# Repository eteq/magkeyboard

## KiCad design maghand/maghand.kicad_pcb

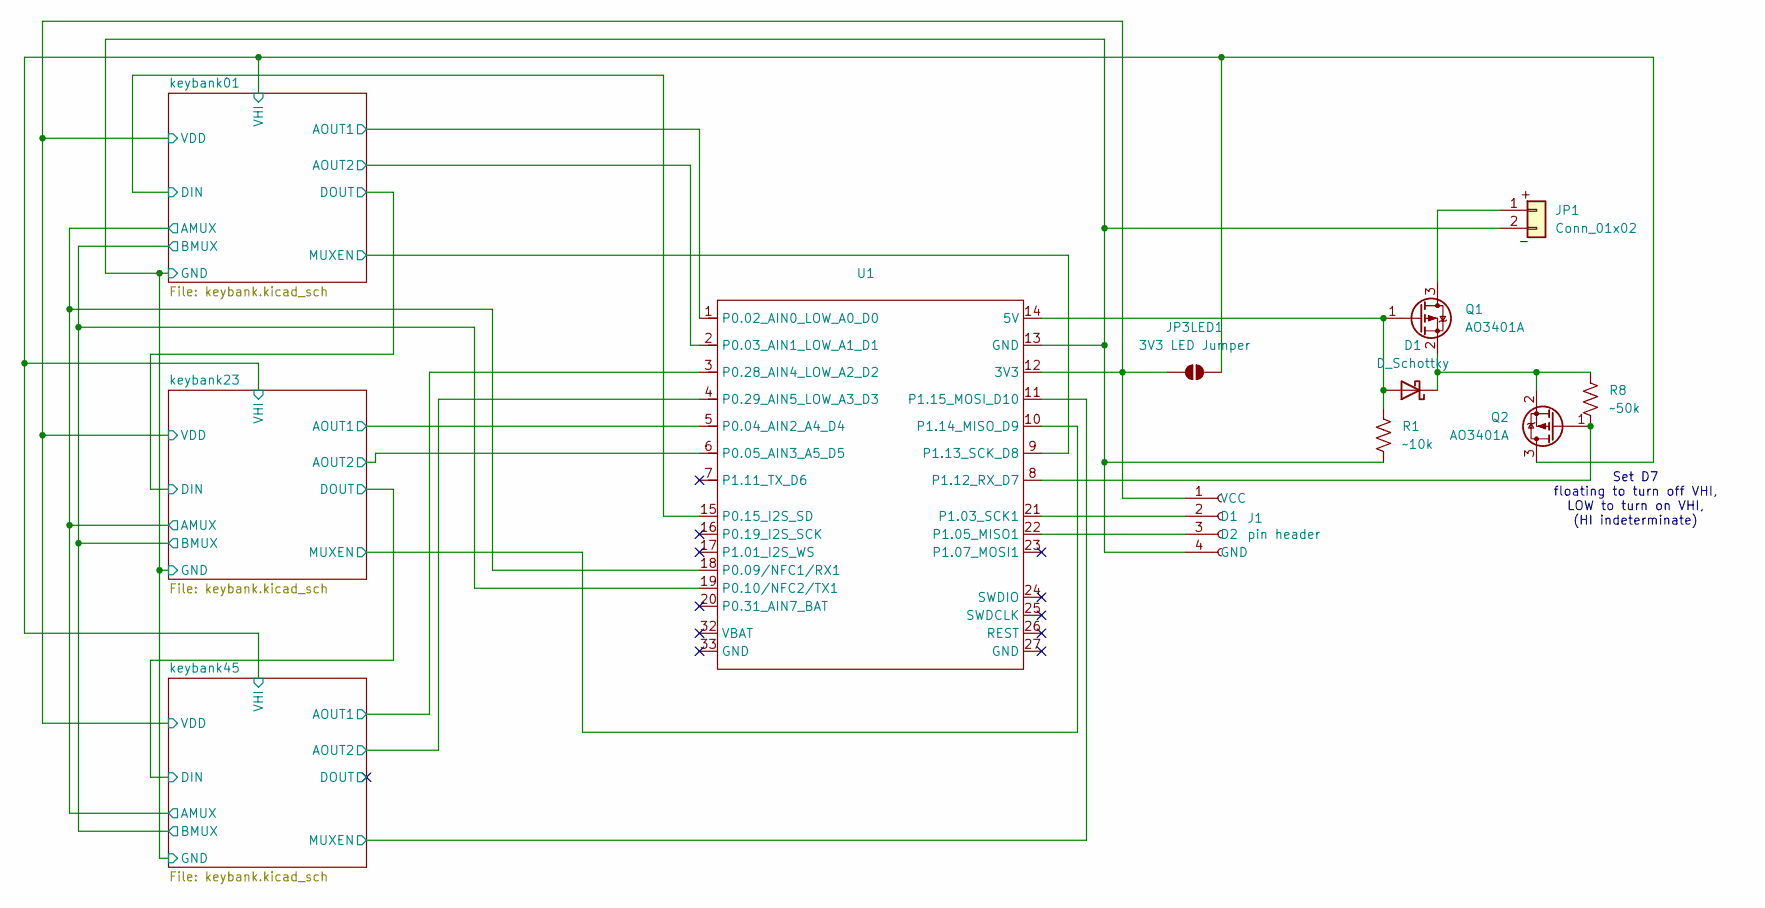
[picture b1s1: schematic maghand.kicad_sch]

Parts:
D1: D_Schottky; D_Powermite_AK
J1: pin header; PinSocket_1x04_P2.54mm_Vertical
JP1: Conn_01x02; JST_PH_S2B-PH-SM4-TB_1x02-1MP_P2.00mm_Horizontal
JP3LED1: 3V3 LED Jumper; SolderJumper-2_P1.3mm_Open_TrianglePad1.0x1.5mm
Q1, Q2: AO3401A; SOT-23
R1: ~10k; R_0805_2012Metric_Pad1.20x1.40mm_HandSolder
R8: ~50k; R_0805_2012Metric_Pad1.20x1.40mm_HandSolder
U1: XIAO-nRF52840-Plus-SMD_bathole

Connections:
/keybank01/AMUX: U1.18 (P0.09/NFC1/RX1); also elsewhere on the board
/keybank01/AOUT1: U1.1 (P0.02_AIN0_LOW_A0_D0); also elsewhere on the board
/keybank01/AOUT2: U1.2 (P0.03_AIN1_LOW_A1_D1); also elsewhere on the board
/keybank01/BMUX: U1.19 (P0.10/NFC2/TX1); also elsewhere on the board
/keybank01/DIN: U1.15 (P0.15_I2S_SD); also elsewhere on the board
/keybank01/GND: J1.4 (GND), JP1.2 (BAT-), R1.2, U1.13 (GND); also elsewhere on the board
/keybank01/MUXEN: U1.9 (P1.13_SCK_D8); also elsewhere on the board
/keybank01/VDD: J1.1 (VCC), JP3LED1.2 (B), U1.12 (3V3); also elsewhere on the board
/keybank01/VHI: JP3LED1.1 (A), Q2.3 (D); also elsewhere on the board
/keybank23/AOUT1: U1.5 (P0.04_AIN2_A4_D4); also elsewhere on the board
/keybank23/AOUT2: U1.6 (P0.05_AIN3_A5_D5); also elsewhere on the board
/keybank23/MUXEN: U1.10 (P1.14_MISO_D9); also elsewhere on the board
/keybank45/AOUT1: U1.3 (P0.28_AIN4_LOW_A2_D2); also elsewhere on the board
/keybank45/AOUT2: U1.4 (P0.29_AIN5_LOW_A3_D3); also elsewhere on the board
/keybank45/MUXEN: U1.11 (P1.15_MOSI_D10); also elsewhere on the board
unnamed: D1.2 (A), Q1.1 (G), R1.1, U1.14 (5V)
unnamed: D1.1 (K), Q1.2 (S), Q2.2 (S), R8.1
unnamed: J1.2 (D1), U1.21 (P1.03_SCK1)
unnamed: J1.3 (D2), U1.22 (P1.05_MISO1)
unnamed: JP1.1 (BAT+), Q1.3 (D)
unnamed: Q2.1 (G), R8.2, U1.8 (P1.12_RX_D7)

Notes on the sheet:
Set D7 floating to turn off VHI, LOW to turn on VHI, (HI indeterminate)

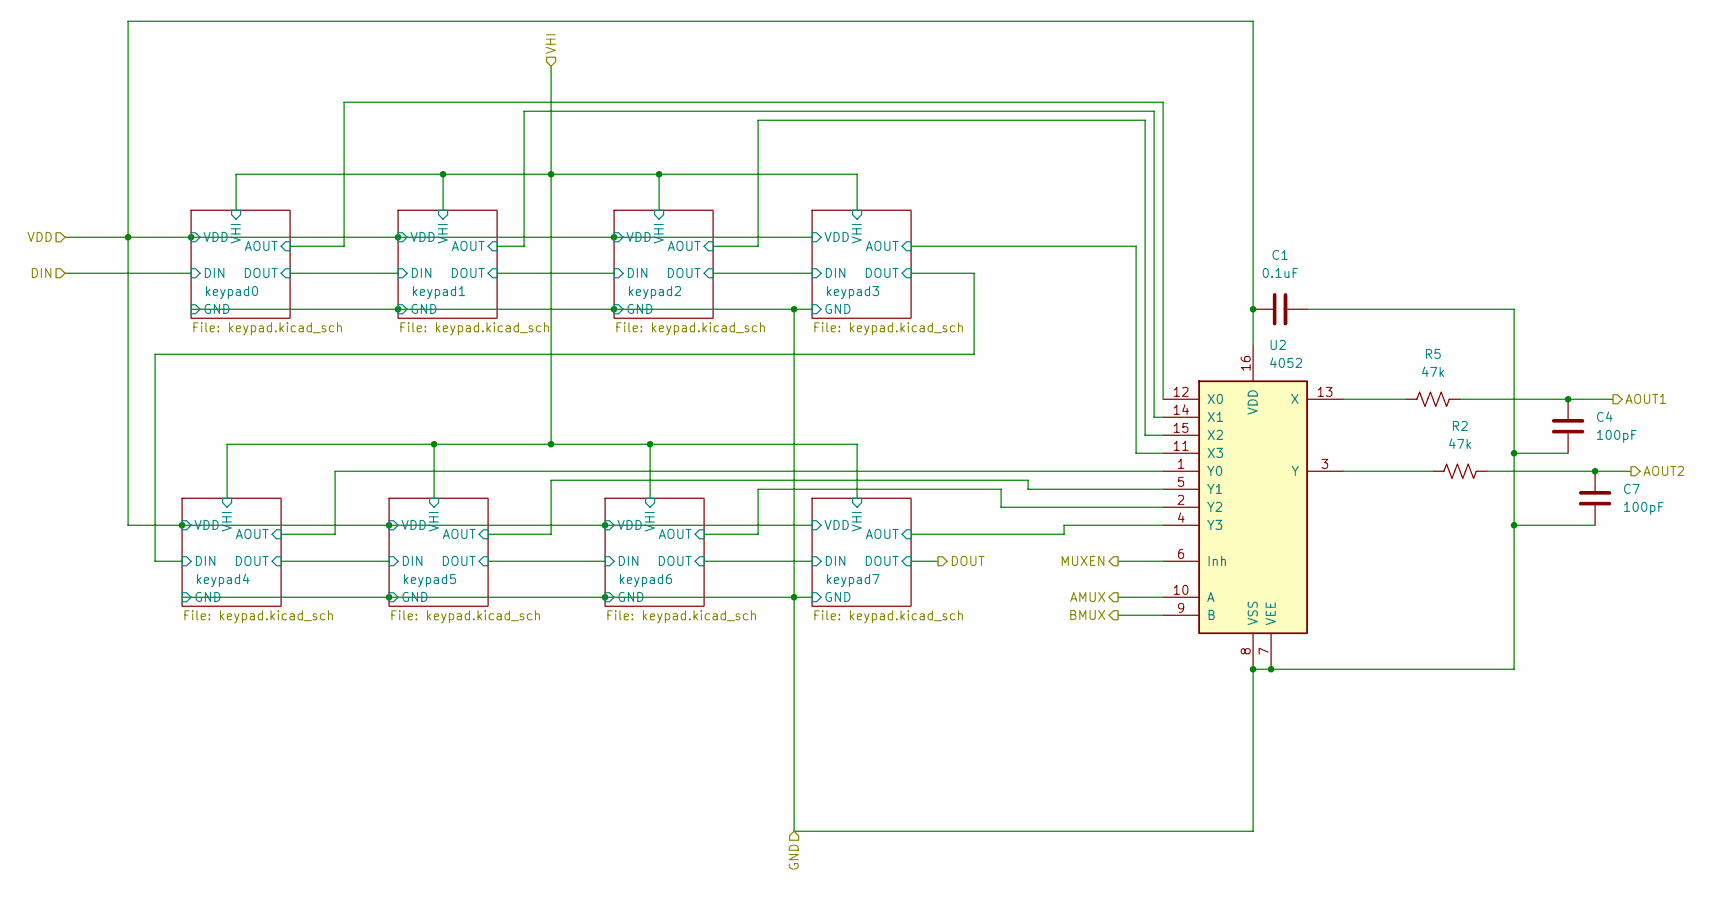
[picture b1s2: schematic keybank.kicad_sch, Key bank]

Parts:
C1: 0.1uF; C_0805_2012Metric_Pad1.18x1.45mm_HandSolder
C4, C7: 100pF; C_0805_2012Metric_Pad1.18x1.45mm_HandSolder
R2, R5: 47k; R_0805_2012Metric_Pad1.20x1.40mm_HandSolder
U2: 4052; SOIC-16_3.9x9.9mm_P1.27mm

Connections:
/keybank01/AMUX: U2.10 (A); also elsewhere on the board
/keybank01/AOUT1: C4.1, R5.2; also elsewhere on the board
/keybank01/AOUT2: C7.1, R2.2; also elsewhere on the board
/keybank01/BMUX: U2.9 (B); also elsewhere on the board
/keybank01/GND: C1.1, C4.2, C7.2, U2.7 (VEE), U2.8 (VSS); also elsewhere on the board
/keybank01/MUXEN: U2.6 (Inh); also elsewhere on the board
/keybank01/VDD: C1.2, U2.16 (VDD); also elsewhere on the board
/keybank01/keypad0/AOUT: U2.12 (X0); also elsewhere on the board
/keybank01/keypad1/AOUT: U2.14 (X1); also elsewhere on the board
/keybank01/keypad2/AOUT: U2.15 (X2); also elsewhere on the board
/keybank01/keypad3/AOUT: U2.11 (X3); also elsewhere on the board
/keybank01/keypad4/AOUT: U2.1 (Y0); also elsewhere on the board
/keybank01/keypad5/AOUT: U2.5 (Y1); also elsewhere on the board
/keybank01/keypad6/AOUT: U2.2 (Y2); also elsewhere on the board
/keybank01/keypad7/AOUT: U2.4 (Y3); also elsewhere on the board
unnamed: R5.1, U2.13 (X)
unnamed: R2.1, U2.3 (Y)

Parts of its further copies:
C2, C3: 0.1uF; C_0805_2012Metric_Pad1.18x1.45mm_HandSolder
C5, C6, C8, C9: 100pF; C_0805_2012Metric_Pad1.18x1.45mm_HandSolder
R3, R4, R6, R7: 47k; R_0805_2012Metric_Pad1.20x1.40mm_HandSolder
U3, U4: 4052; SOIC-16_3.9x9.9mm_P1.27mm

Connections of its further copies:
/keybank01/AMUX: U3.10 (A), U4.10 (A); also elsewhere on the board
/keybank01/BMUX: U3.9 (B), U4.9 (B); also elsewhere on the board
/keybank01/GND: C2.1, C3.1, C5.2, C6.2, C8.2, C9.2, U3.7 (VEE), U3.8 (VSS), U4.7 (VEE), U4.8 (VSS); also elsewhere on the board
/keybank01/VDD: C2.2, C3.2, U3.16 (VDD), U4.16 (VDD); also elsewhere on the board
/keybank23/AOUT1: C5.1, R6.2; also elsewhere on the board
/keybank23/AOUT2: C8.1, R3.2; also elsewhere on the board
/keybank23/MUXEN: U3.6 (Inh); also elsewhere on the board
/keybank23/keypad0/AOUT: U3.12 (X0); also elsewhere on the board
/keybank23/keypad1/AOUT: U3.14 (X1); also elsewhere on the board
/keybank23/keypad2/AOUT: U3.15 (X2); also elsewhere on the board
/keybank23/keypad3/AOUT: U3.11 (X3); also elsewhere on the board
/keybank23/keypad4/AOUT: U3.1 (Y0); also elsewhere on the board
/keybank23/keypad5/AOUT: U3.5 (Y1); also elsewhere on the board
/keybank23/keypad6/AOUT: U3.2 (Y2); also elsewhere on the board
/keybank23/keypad7/AOUT: U3.4 (Y3); also elsewhere on the board
/keybank45/AOUT1: C6.1, R7.2; also elsewhere on the board
/keybank45/AOUT2: C9.1, R4.2; also elsewhere on the board
/keybank45/MUXEN: U4.6 (Inh); also elsewhere on the board
/keybank45/keypad0/AOUT: U4.12 (X0); also elsewhere on the board
/keybank45/keypad1/AOUT: U4.14 (X1); also elsewhere on the board
/keybank45/keypad2/AOUT: U4.15 (X2); also elsewhere on the board
/keybank45/keypad3/AOUT: U4.11 (X3); also elsewhere on the board
/keybank45/keypad4/AOUT: U4.1 (Y0); also elsewhere on the board
/keybank45/keypad5/AOUT: U4.5 (Y1); also elsewhere on the board
/keybank45/keypad6/AOUT: U4.2 (Y2); also elsewhere on the board
/keybank45/keypad7/AOUT: U4.4 (Y3)
unnamed: R6.1, U3.13 (X)
unnamed: R3.1, U3.3 (Y)
unnamed: R7.1, U4.13 (X)
unnamed: R4.1, U4.3 (Y)

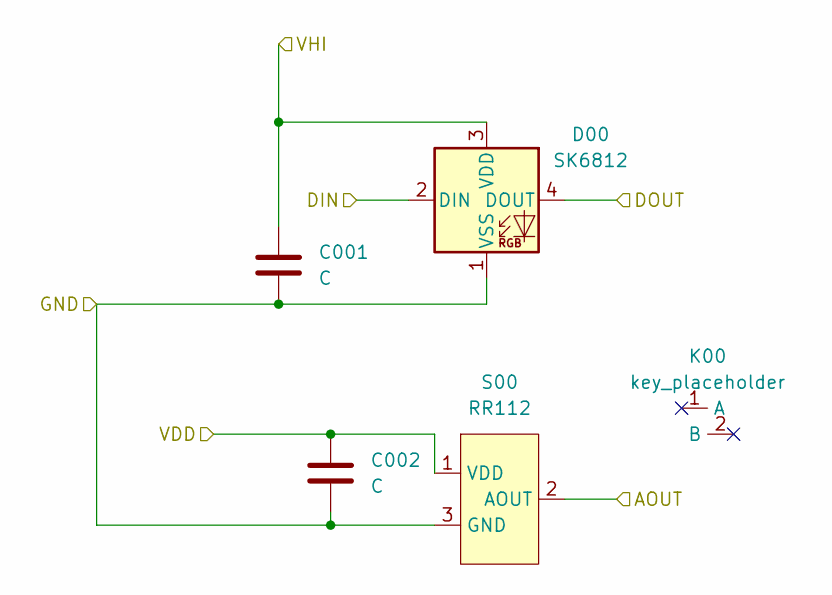
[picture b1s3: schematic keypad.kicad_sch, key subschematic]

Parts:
C001, C002: C; C_0805_2012Metric_Pad1.18x1.45mm_HandSolder
D00: SK6812; LED_SK6812_PLCC4_5.0x5.0mm_P3.2mm
K00: key_placeholder; Key Holder
S00: RR112; SOT-23_Handsoldering

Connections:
/keybank01/DIN: D00.2 (DIN); also elsewhere on the board
/keybank01/GND: C001.2, C002.2, D00.1 (VSS), S00.3 (GND); also elsewhere on the board
/keybank01/VDD: C002.1, S00.1 (VDD); also elsewhere on the board
/keybank01/VHI: C001.1, D00.3 (VDD); also elsewhere on the board
/keybank01/keypad0/AOUT: S00.2 (AOUT); also elsewhere on the board
/keybank01/keypad0/DOUT: D00.4 (DOUT); also elsewhere on the board

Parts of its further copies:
C011, C012, C021, C022, C031, C032, C101, C102, C111, C112, C121, C122, C131, C132, C201, C202, C211, C212, C221, C222, C231, C232, C301, C302, C311, C312, C321, C322, C331, C332, C401, C402, C411, C412, C421, C422, C431, C432, C501, C502, C511, C512, C521, C522: C; C_0805_2012Metric_Pad1.18x1.45mm_HandSolder
D01, D02, D03, D10, D11, D12, D13, D20, D21, D22, D23, D30, D31, D32, D33, D40, D41, D42, D43, D50, D51, D52: SK6812; LED_SK6812_PLCC4_5.0x5.0mm_P3.2mm
K01, K02, K03, K10, K11, K12, K13, K20, K21, K22, K23, K30, K31, K32, K33, K40, K41, K42, K43, K50, K51, K52: key_placeholder; Key Holder
S01, S02, S03, S10, S11, S12, S13, S20, S21, S22, S23, S30, S31, S32, S33, S40, S41, S42, S43, S50, S51, S52: RR112; SOT-23_Handsoldering

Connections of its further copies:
/keybank01/DOUT: D13.4 (DOUT), D20.2 (DIN)
/keybank01/GND: C011.2, C012.2, C021.2, C022.2, C031.2, C032.2, C101.2, C102.2, C111.2, C112.2, C121.2, C122.2, C131.2, C132.2, C201.2, C202.2, C211.2, C212.2, C221.2, C222.2, C231.2, C232.2, C301.2, C302.2, C311.2, C312.2, C321.2, C322.2, C331.2, C332.2, C401.2, C402.2, C411.2, C412.2, C421.2, C422.2, C431.2, C432.2, C501.2, C502.2, C511.2, C512.2, C521.2, C522.2, D01.1 (VSS), D02.1 (VSS), D03.1 (VSS), D10.1 (VSS), D11.1 (VSS), D12.1 (VSS), D13.1 (VSS), D20.1 (VSS), D21.1 (VSS), D22.1 (VSS), D23.1 (VSS), D30.1 (VSS), D31.1 (VSS), D32.1 (VSS), D33.1 (VSS), D40.1 (VSS), D41.1 (VSS), D42.1 (VSS), D43.1 (VSS), D50.1 (VSS), D51.1 (VSS), D52.1 (VSS), S01.3 (GND), S02.3 (GND), S03.3 (GND), S10.3 (GND), S11.3 (GND), S12.3 (GND), S13.3 (GND), S20.3 (GND), S21.3 (GND), S22.3 (GND), S23.3 (GND), S30.3 (GND), S31.3 (GND), S32.3 (GND), S33.3 (GND), S40.3 (GND), S41.3 (GND), S42.3 (GND), S43.3 (GND), S50.3 (GND), S51.3 (GND), S52.3 (GND); also elsewhere on the board
/keybank01/VDD: C012.1, C022.1, C032.1, C102.1, C112.1, C122.1, C132.1, C202.1, C212.1, C222.1, C232.1, C302.1, C312.1, C322.1, C332.1, C402.1, C412.1, C422.1, C432.1, C502.1, C512.1, C522.1, S01.1 (VDD), S02.1 (VDD), S03.1 (VDD), S10.1 (VDD), S11.1 (VDD), S12.1 (VDD), S13.1 (VDD), S20.1 (VDD), S21.1 (VDD), S22.1 (VDD), S23.1 (VDD), S30.1 (VDD), S31.1 (VDD), S32.1 (VDD), S33.1 (VDD), S40.1 (VDD), S41.1 (VDD), S42.1 (VDD), S43.1 (VDD), S50.1 (VDD), S51.1 (VDD), S52.1 (VDD); also elsewhere on the board
/keybank01/VHI: C011.1, C021.1, C031.1, C101.1, C111.1, C121.1, C131.1, C201.1, C211.1, C221.1, C231.1, C301.1, C311.1, C321.1, C331.1, C401.1, C411.1, C421.1, C431.1, C501.1, C511.1, C521.1, D01.3 (VDD), D02.3 (VDD), D03.3 (VDD), D10.3 (VDD), D11.3 (VDD), D12.3 (VDD), D13.3 (VDD), D20.3 (VDD), D21.3 (VDD), D22.3 (VDD), D23.3 (VDD), D30.3 (VDD), D31.3 (VDD), D32.3 (VDD), D33.3 (VDD), D40.3 (VDD), D41.3 (VDD), D42.3 (VDD), D43.3 (VDD), D50.3 (VDD), D51.3 (VDD), D52.3 (VDD); also elsewhere on the board
/keybank01/keypad0/DOUT: D01.2 (DIN); also elsewhere on the board
/keybank01/keypad1/AOUT: S01.2 (AOUT); also elsewhere on the board
/keybank01/keypad1/DOUT: D01.4 (DOUT), D02.2 (DIN)
/keybank01/keypad2/AOUT: S02.2 (AOUT); also elsewhere on the board
/keybank01/keypad2/DOUT: D02.4 (DOUT), D03.2 (DIN)
/keybank01/keypad3/AOUT: S03.2 (AOUT); also elsewhere on the board
/keybank01/keypad3/DOUT: D03.4 (DOUT), D10.2 (DIN)
/keybank01/keypad4/AOUT: S10.2 (AOUT); also elsewhere on the board
/keybank01/keypad4/DOUT: D10.4 (DOUT), D11.2 (DIN)
/keybank01/keypad5/AOUT: S11.2 (AOUT); also elsewhere on the board
/keybank01/keypad5/DOUT: D11.4 (DOUT), D12.2 (DIN)
/keybank01/keypad6/AOUT: S12.2 (AOUT); also elsewhere on the board
/keybank01/keypad6/DOUT: D12.4 (DOUT), D13.2 (DIN)
/keybank01/keypad7/AOUT: S13.2 (AOUT); also elsewhere on the board
/keybank23/DOUT: D33.4 (DOUT), D40.2 (DIN)
/keybank23/keypad0/AOUT: S20.2 (AOUT); also elsewhere on the board
/keybank23/keypad0/DOUT: D20.4 (DOUT), D21.2 (DIN)
/keybank23/keypad1/AOUT: S21.2 (AOUT); also elsewhere on the board
/keybank23/keypad1/DOUT: D21.4 (DOUT), D22.2 (DIN)
/keybank23/keypad2/AOUT: S22.2 (AOUT); also elsewhere on the board
/keybank23/keypad2/DOUT: D22.4 (DOUT), D23.2 (DIN)
/keybank23/keypad3/AOUT: S23.2 (AOUT); also elsewhere on the board
/keybank23/keypad3/DOUT: D23.4 (DOUT), D30.2 (DIN)
/keybank23/keypad4/AOUT: S30.2 (AOUT); also elsewhere on the board
/keybank23/keypad4/DOUT: D30.4 (DOUT), D31.2 (DIN)
/keybank23/keypad5/AOUT: S31.2 (AOUT); also elsewhere on the board
/keybank23/keypad5/DOUT: D31.4 (DOUT), D32.2 (DIN)
/keybank23/keypad6/AOUT: S32.2 (AOUT); also elsewhere on the board
/keybank23/keypad6/DOUT: D32.4 (DOUT), D33.2 (DIN)
/keybank23/keypad7/AOUT: S33.2 (AOUT); also elsewhere on the board
/keybank45/keypad0/AOUT: S40.2 (AOUT); also elsewhere on the board
/keybank45/keypad0/DOUT: D40.4 (DOUT), D41.2 (DIN)
/keybank45/keypad1/AOUT: S41.2 (AOUT); also elsewhere on the board
/keybank45/keypad1/DOUT: D41.4 (DOUT), D42.2 (DIN)
/keybank45/keypad2/AOUT: S42.2 (AOUT); also elsewhere on the board
/keybank45/keypad2/DOUT: D42.4 (DOUT), D43.2 (DIN)
/keybank45/keypad3/AOUT: S43.2 (AOUT); also elsewhere on the board
/keybank45/keypad3/DOUT: D43.4 (DOUT), D50.2 (DIN)
/keybank45/keypad4/AOUT: S50.2 (AOUT); also elsewhere on the board
/keybank45/keypad4/DOUT: D50.4 (DOUT), D51.2 (DIN)
/keybank45/keypad5/AOUT: S51.2 (AOUT); also elsewhere on the board
/keybank45/keypad5/DOUT: D51.4 (DOUT), D52.2 (DIN)
/keybank45/keypad6/AOUT: S52.2 (AOUT); also elsewhere on the board
/keybank45/keypad6/DOUT: D52.4 (DOUT)

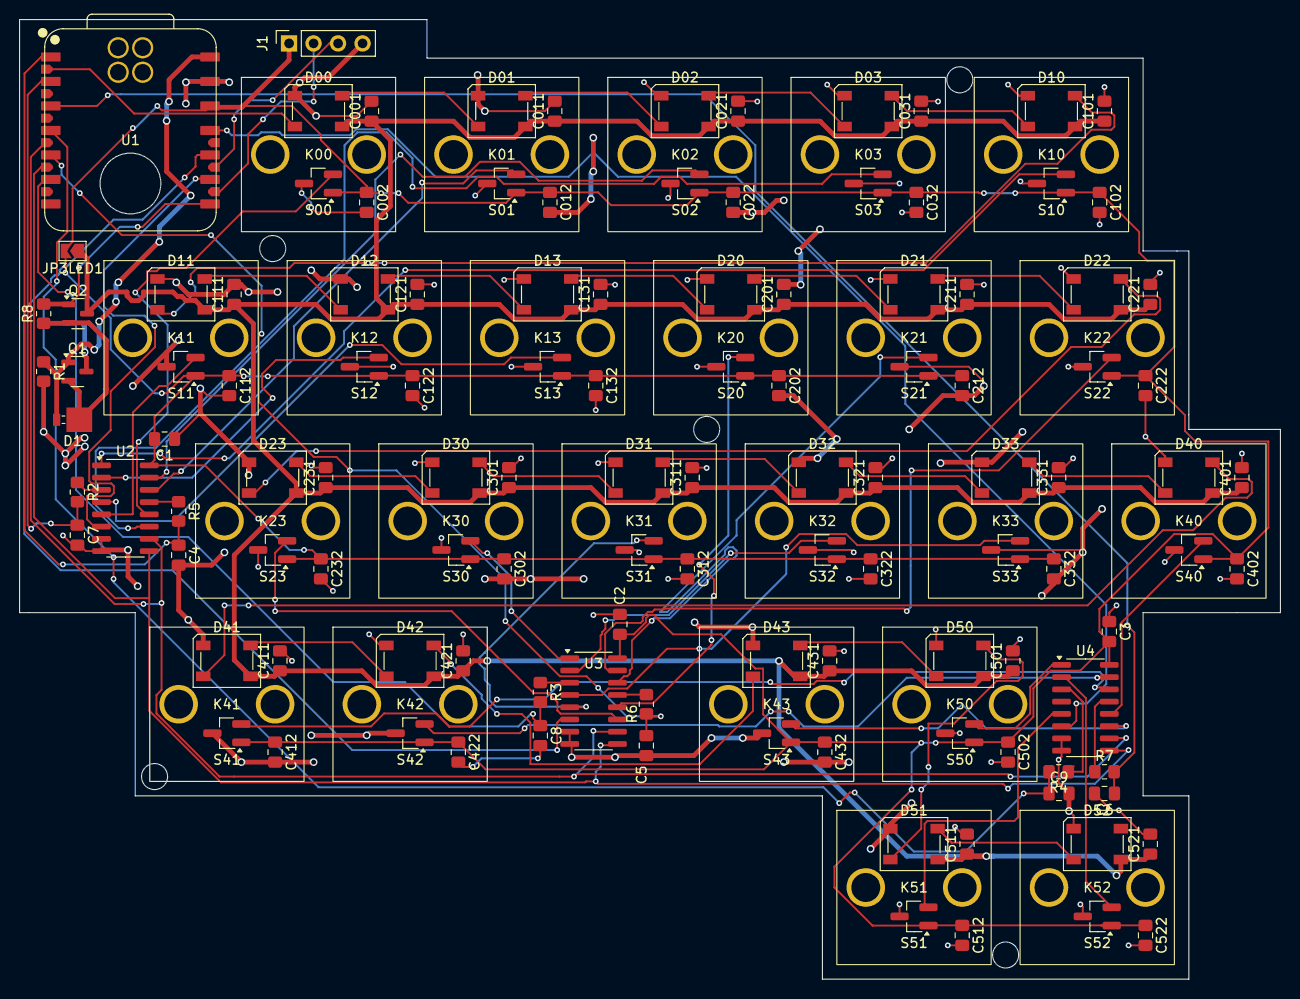
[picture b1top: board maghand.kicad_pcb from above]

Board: 2 copper layers, 130.8 x 99.5 mm, 142 parts (1 on the bottom side), 72 nets.

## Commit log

2025-11-02 gitig
2025-11-02 code
2025-11-02 add pcb
2026-01-11 added initial working firmware
2026-01-11 remove ci from firmware
2026-01-11 a few updates to plot testing
2026-01-11 add missing calib
2026-01-11 add sense board led setter
2026-01-11 working spi-driven leds
2026-01-11 cargo fmt
2026-01-11 working imu
2026-01-12 add gyro
2026-01-12 power notes
2026-01-12 dc/dc note
2026-01-13 testing adc multi-channel reading
2026-01-17 modifications for making test measurements
2026-01-18 functioning core algorithm for clicking
2026-01-24 more testing
2026-01-26 working sampling mode
2026-01-26 continued algorithmic experimentation
2026-01-26 remove some left over bits
2026-01-26 added important missing files!
2026-01-27 working keypress version
2026-01-27 test data rejiggering
2026-01-27 remove unneeded code
2026-01-28 one more unneeded bit
2026-01-28 minor format fix
2026-01-28 add optional adc printing feature
2026-01-29 incomplete usb breakout function
2026-01-29 borrowing is hard
2026-01-29 compiling usb version
2026-01-29 conceptually working usb keyboard machinery
2026-01-30 add code for making rust keymap structure
2026-01-30 working keymap
2026-01-30 switched to pubsub instead of channel
2026-01-30 fix testing mode
2026-02-07 add some power testing bits
